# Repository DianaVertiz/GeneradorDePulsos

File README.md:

# GeneradorDePulsos
Programa generador de pulsos de frecuencia, duración y amplitud variables

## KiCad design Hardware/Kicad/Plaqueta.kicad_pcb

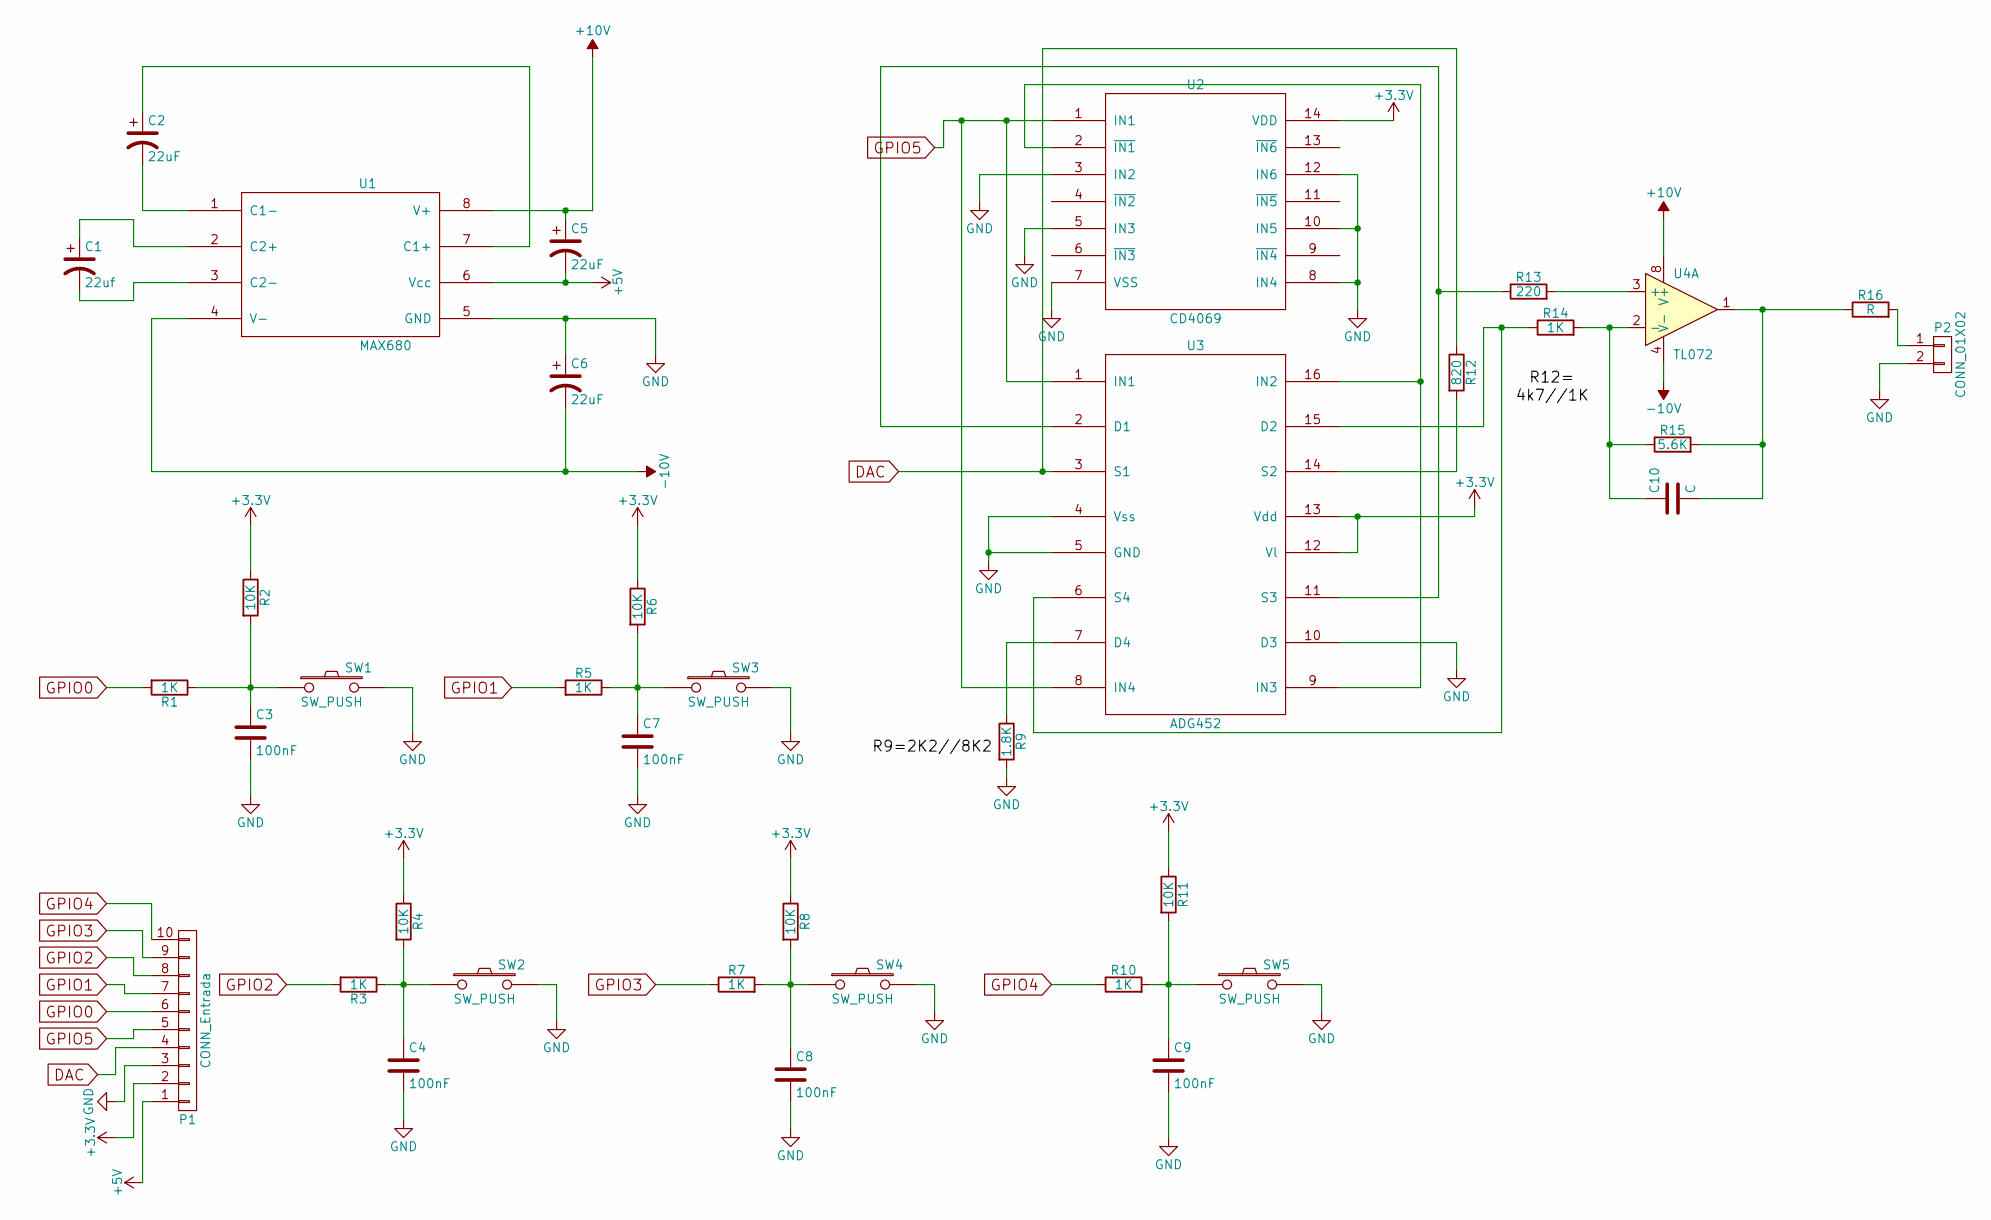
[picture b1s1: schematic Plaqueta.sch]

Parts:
C1: 22uf; C_Radial_D5_L11_P2.5
C2, C5, C6: 22uF; C_Radial_D5_L11_P2.5
C3, C4, C7, C8, C9: 100nF; C_0805_HandSoldering
C10: C; C_0805_HandSoldering
P1: CONN_Entrada; Pin_Header_Straight_1x10
P2: CONN_01X02; Pin_Header_Straight_1x02
R1, R3, R5, R7, R10, R14: 1K; R_0805_HandSoldering
R2, R4, R6, R8, R11: 10K; R_0805_HandSoldering
R9: 1.8K; R_0805_HandSoldering
R12: 820; R_0805_HandSoldering
R13: 220; R_0805_HandSoldering
R15: 5.6K; R_0805_HandSoldering
R16: R; R_0805_HandSoldering
SW1, SW2, SW3, SW4, SW5: SW_PUSH; SW_PUSH-12mm
U1: MAX680; DIP-8_W7.62mm_LongPads
U2: CD4069; DIP-14_W7.62mm_LongPads
U3: ADG452; SOIC-16_3.9x9.9mm_Pitch1.27mm
U4: TL072; DIP-8_W7.62mm_LongPads

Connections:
10V: C5.1, U1.8 (V+), U4.8 (V+)
+3V3: P1.2, R2.1, R4.1, R6.1, R8.1, R11.1, U2.14 (VDD), U3.12 (Vl), U3.13 (Vdd)
+5V: C5.2, P1.1, U1.6 (Vcc)
-10V: C6.2, U1.4 (V-), U4.4 (V-)
DAC: P1.4, R12.1, U3.3 (S1)
GND: C3.2, C4.2, C6.1, C7.2, C8.2, C9.2, P1.3, P2.2, R9.2, SW1.2, SW2.2, SW3.2, SW4.2, SW5.2, U1.5 (GND), U2.3 (IN2), U2.5 (IN3), U2.7 (VSS), U2.8 (IN4), U2.10 (IN5), U2.12 (IN6), U3.4 (Vss), U3.5 (GND), U3.10 (D3)
GPIO0: P1.6, R1.2
GPIO1: P1.7, R5.2
GPIO2: P1.8, R3.2
GPIO3: P1.9, R7.1
GPIO4: P1.10, R10.1
GPIO5: P1.5, U2.1 (IN1), U3.1 (IN1), U3.8 (IN4)
unnamed: C1.1, U1.2 (C2+)
unnamed: C1.2, U1.3 (C2-)
unnamed: C2.1, U1.7 (C1+)
unnamed: C2.2, U1.1 (C1-)
unnamed: C3.1, R1.1, R2.2, SW1.1
unnamed: C4.1, R3.1, R4.2, SW2.1
unnamed: C7.1, R5.1, R6.2, SW3.1
unnamed: C8.1, R7.2, R8.2, SW4.1
unnamed: C9.1, R10.2, R11.2, SW5.1
unnamed: C10.1, R14.2, R15.1, U4.2 (-)
unnamed: C10.2, R15.2, R16.1, U4.1
unnamed: P2.1, R16.2
unnamed: R9.1, U3.7 (D4)
unnamed: R12.2, U3.14 (S2)
unnamed: R13.1, U3.2 (D1), U3.11 (S3)
unnamed: R13.2, U4.3 (+)
unnamed: R14.1, U3.6 (S4), U3.15 (D2)
unnamed: U2.2 (~IN1), U3.9 (IN3), U3.16 (IN2)

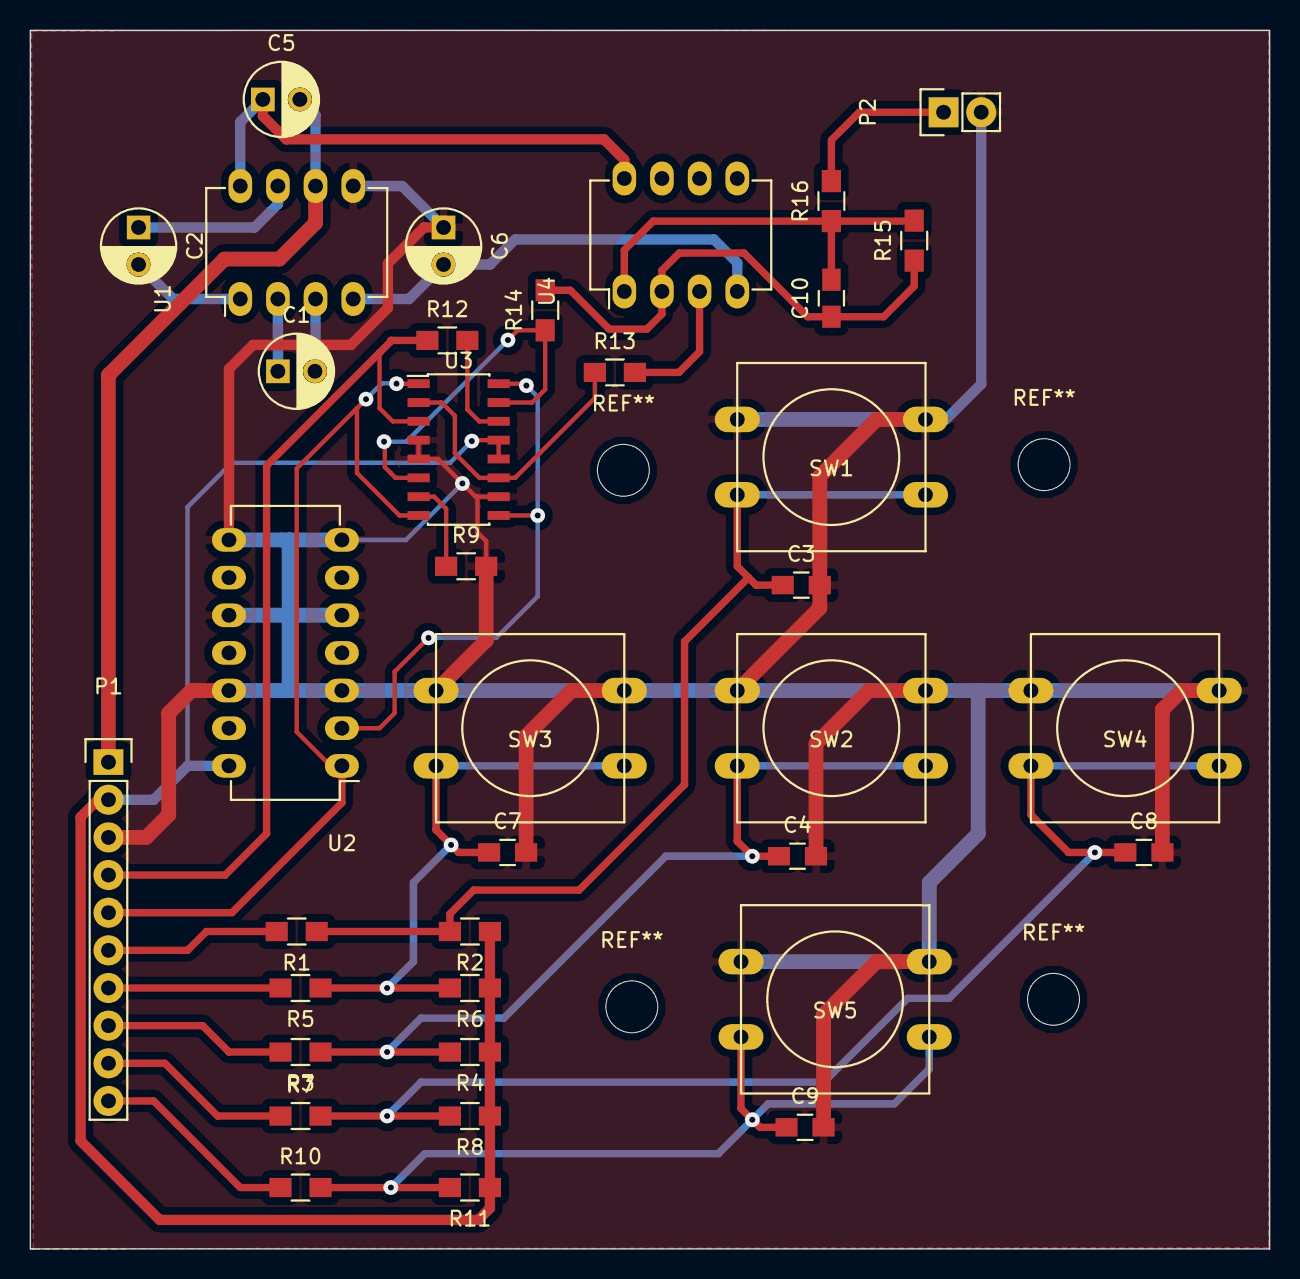
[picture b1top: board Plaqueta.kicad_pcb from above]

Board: 2 copper layers, 83.6 x 82.2 mm, 37 parts (0 on the bottom side), 30 nets.

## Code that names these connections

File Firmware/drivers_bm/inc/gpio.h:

/* Copyright 2016, 
 * Eduardo Filomena
 * efilomena@bioingenieria.edu.ar
 * Juan Manuel Reta
 * jmrera@bioingenieria.edu.ar
 * Facultad de Ingeniería
 * Universidad Nacional de Entre Ríos
 * Argentina
 *
 * All rights reserved.
 *
 * Redistribution and use in source and binary forms, with or without
 * modification, are permitted provided that the following conditions are met:
 *
 * 1. Redistributions of source code must retain the above copyright notice,
 *    this list of conditions and the following disclaimer.
 *
 * 2. Redistributions in binary form must reproduce the above copyright notice,
 *    this list of conditions and the following disclaimer in the documentation
 *    and/or other materials provided with the distribution.
 *
 * 3. Neither the name of the copyright holder nor the names of its
 *    contributors may be used to endorse or promote products derived from this
 *    software without specific prior written permission.
 *
 * THIS SOFTWARE IS PROVIDED BY THE COPYRIGHT HOLDERS AND CONTRIBUTORS "AS IS"
 * AND ANY EXPRESS OR IMPLIED WARRANTIES, INCLUDING, BUT NOT LIMITED TO, THE
 * IMPLIED WARRANTIES OF MERCHANTABILITY AND FITNESS FOR A PARTICULAR PURPOSE
 * ARE DISCLAIMED. IN NO EVENT SHALL THE COPYRIGHT HOLDER OR CONTRIBUTORS BE
 * LIABLE FOR ANY DIRECT, INDIRECT, INCIDENTAL, SPECIAL, EXEMPLARY, OR
 * CONSEQUENTIAL DAMAGES (INCLUDING, BUT NOT LIMITED TO, PROCUREMENT OF
 * SUBSTITUTE GOODS OR SERVICES; LOSS OF USE, DATA, OR PROFITS; OR BUSINESS
 * INTERRUPTION) HOWEVER CAUSED AND ON ANY THEORY OF LIABILITY, WHETHER IN
 * CONTRACT, STRICT LIABILITY, OR TORT (INCLUDING NEGLIGENCE OR OTHERWISE)
 * ARISING IN ANY WAY OUT OF THE USE OF THIS SOFTWARE, EVEN IF ADVISED OF THE
 * POSSIBILITY OF SUCH DAMAGE.
 *
 */
#ifndef GPIO_H
#define GIPO_H


/*==================[inclusions]=============================================*/
#include "stdint.h"
#include "chip.h"
#define BtnUp	GPIO0
#define BtnDown	GPIO4
#define BtnLeft GPIO1
#define BtnRight GPIO3
#define BtnEnter GPIO2

/*==================[macros]=================================================*/
#define lpc4337            1
#define mk60fx512vlq15     2

/*==================[typedef]================================================*/

/*==================[external data declaration]==============================*/
/** \brief Definition of constants to reference the EDU-CIAA GPIO.
 **
 **/
enum GPIO_NUM {GPIO0,GPIO1,GPIO2,GPIO3,GPIO4,GPIO5,GPIO6,GPIO7,GPIO8};


/** \brief Definition of constants to control the EDU-CIAA GPIO.
 **
 **/
enum GPIO_CONFIG {INPUT,OUTPUT,INPUT_PUP,INPUT_PDN_INPUT_PUP_PDN};

#define OUTPUT   1
#define INPUT    0


/*==================[external functions declaration]=========================*/

/** \brief Initialization function of EDU-CIAA GPIO
 **
 ** 
 ** \return TRUE if no error
 **/
uint8_t Init_GPIO(void);

/** \brief Direction setting of  GPIO
 **
 ** 
 ** \param[in] GPIO number (GPIO0... GPIO8)  and config (INPUT,OUTPUT, INPUT_PUP.....)
 ** 
 ** \return TRUE if no error
 **/
uint8_t GPIO_Set_Dir(uint8_t gpio_num,uint8_t gpio_config);
 
/** \brief Function to write on a specific GPIO 
 ** 
 ** \param[in] GPIO number (GPIO0... GPIO8) and status (0 or 1,  TRUE or FALSE)
 **
 ** \return FALSE if an error occurs, in other case returns TRUE
 **/
uint8_t GPIO_Write(uint8_t gpio_num, uint8_t status);

/** \brief Function to read a specific GPIO 
 ** 
 ** \param[in] GPIO number (GPIO0... GPIO8)
 **
 ** \return 0 or 1
 **/
uint8_t GPIO_Read(uint8_t gpio_num);



/** @} doxygen end group definition */
/** @} doxygen end group definition */
/** @} doxygen end group definition */
/*==================[end of file]============================================*/
#endif /* #ifndef GPIO_H */

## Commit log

2016-11-14 :circus_tent: Added .gitattributes & .gitignore files
2016-11-14 Carpeta Firmware
    Firmware para edu-ciaa
2016-11-14 Carpeta Software
    Programa en QT
2016-11-14 Carpeta Hardware
    Esquemático y PCB realizado en Kicad
2016-11-24 Carpeta Firmware
2016-11-24 Agregado polaridad de pulsos
2016-12-13 Cambios 13/12/16
2017-01-02 Conexiones display-plaqueta-educiaa
2017-01-19 Corregido
2017-01-29 Modificado comunicación serie
    Agregado la comunicación educiaa->qt
2017-02-05 Mejoras en el menu
2017-02-08 Cambios en QT
2017-03-07 Cambio en el menú
2017-03-07 Cambios en el menu
2017-03-14 Manual
2017-08-21 Agregado Led para controlar relé
    GPIO5 Led de signo
    GPIO8 Led del gabinete
    GPIO6 Led del relé
2017-08-25 delay_rele
    Agregado en pulsos.h la variable para tiempo de espera para disparo del relé
